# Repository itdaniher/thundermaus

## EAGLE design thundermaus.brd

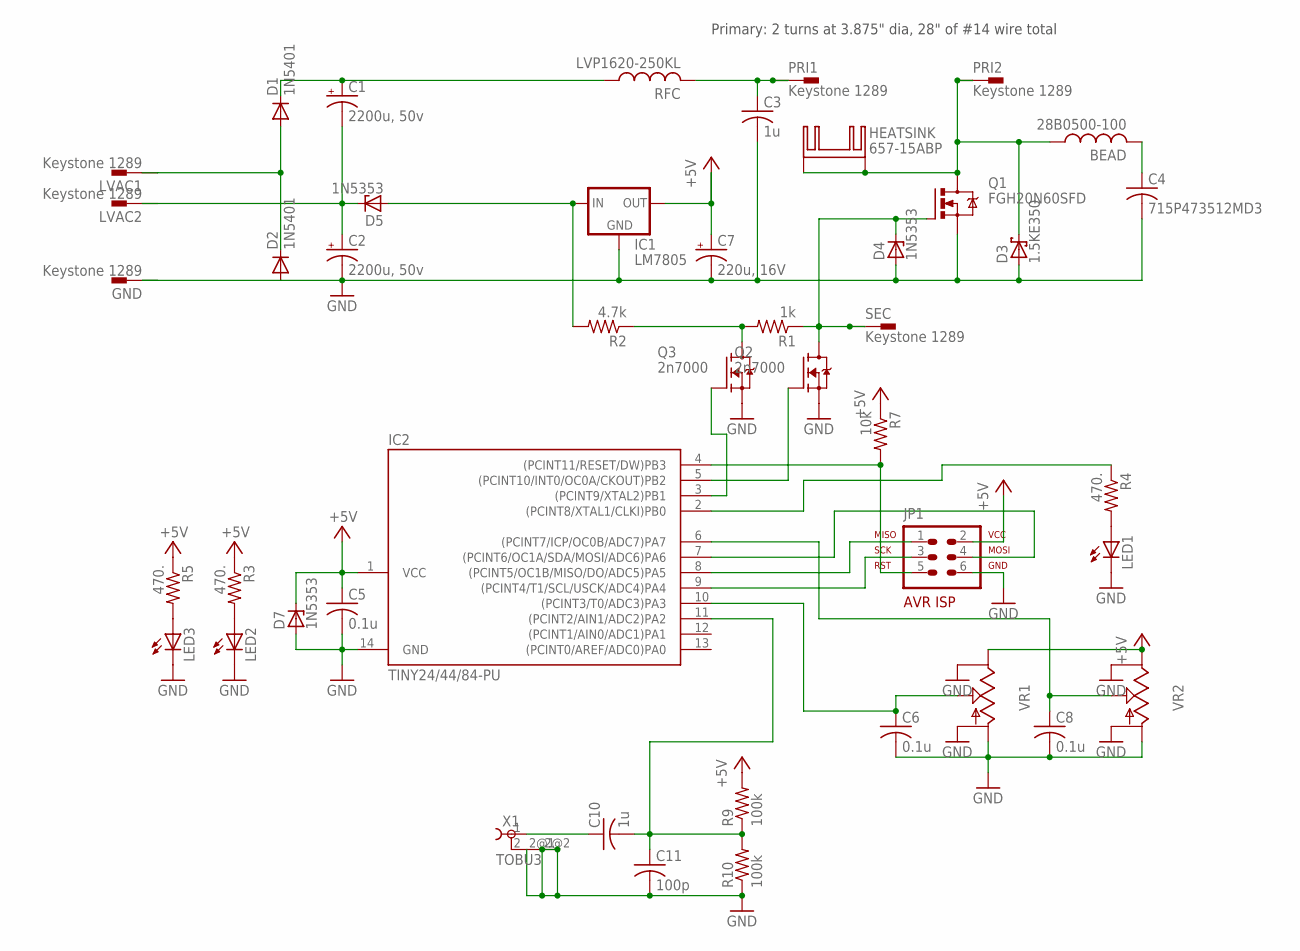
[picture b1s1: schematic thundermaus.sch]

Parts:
BEAD: 28B0500-100; 0207/10
C1, C2: 2200u, 50v; E7,5-16
C3: 1u; C225-062X268
C4: 715P473512MD3; C325-182X374
C5, C6, C8: 0.1u; C025-025X050
C7: 220u, 16V; E2,5-7
C10: 1u; C025-025X050
C11: 100p; C025-025X050
D1, D2: 1N5401; DO201-15
D3: 1.5KE350; DO201T15
D4, D5, D7: 1N5353; C1702-15
GND: Keystone 1289; F061.060
HEATSINK: 657-15ABP; SK129
IC1: LM7805; 78XXS
IC2: TINY24/44/84-PU; DIL14
JP1: AVR-ISP-6VERT; AVR-ISP-6
LED1, LED2, LED3: LED5MM
LVAC1, LVAC2: Keystone 1289; F061.060
PRI1, PRI2: Keystone 1289; F061.060
Q1: FGH20N60SFD; TO247BV
Q2, Q3: 2n7000; TO237-SW
R1: 1k; 0207/10
R2: 4.7k; 0207/10
R3, R4, R5: 470.; 0207/10
R7: 10k; 0207/10
R9, R10: 100k; 0207/10
RFC: LVP1620-250KL; TJ4-U1
SEC: Keystone 1289; F061.060
VR1, VR2: PTV09
X1: TOBU3

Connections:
+5V: C5.1, C7.+, D7.C, IC1.OUT, IC2.1 (VCC), JP1.2, R3.1, R5.1, R7.1, R9.2, VR1.P1 (E), VR2.P1 (E)
GND: C2.-, C3.2, C4.2, C5.2, C6.2, C7.-, C8.2, C11.2, D2.A, D3.A, D4.A, D7.A, GND.A1 (1), GND.A2 (1.1), IC1.GND, IC2.14 (GND), JP1.6, LED1.K (C), LED2.K (C), LED3.K (C), Q1.S, Q2.3 (S), Q3.3 (S), R10.1, VR1.P3 (A), VR1.P$4, VR1.P$5, VR2.P3 (A), VR2.P$4, VR2.P$5, X1.2, X1.2@1 (3), X1.2@2 (4)
unnamed: LED2.A, R3.2
unnamed: D5.A, IC1.IN, R2.2
unnamed: IC2.5 ((PCINT10/INT0/OC0A/CKOUT)PB2), Q2.2 (G)
unnamed: C1.+, D1.C, RFC.1
unnamed: C3.1, PRI1.A1 (1), PRI1.A2 (1.1), RFC.2
unnamed: Q3.1 (D), R1.2, R2.1
unnamed: BEAD.2, C4.1
unnamed: IC2.3 ((PCINT9/XTAL2)PB1), Q3.2 (G)
unnamed: IC2.7 ((PCINT6/OC1A/SDA/MOSI/ADC6)PA6), JP1.4
unnamed: LED3.A, R5.2
unnamed: D4.C, Q1.G, Q2.1 (D), R1.1, SEC.A1 (1), SEC.A2 (1.1)
unnamed: LED1.A, R4.2
unnamed: IC2.8 ((PCINT5/OC1B/MISO/DO/ADC5)PA5), JP1.1
unnamed: IC2.9 ((PCINT4/T1/SCL/USCK/ADC4)PA4), JP1.3
unnamed: IC2.4 ((PCINT11/RESET/DW)PB3), JP1.5, R7.2
unnamed: C6.1, IC2.10 ((PCINT3/T0/ADC3)PA3), VR1.P2 (S)
unnamed: IC2.2 ((PCINT8/XTAL1/CLKI)PB0), R4.1
unnamed: BEAD.1, D3.C, HEATSINK.A2,5, HEATSINK.B2,5, PRI2.A1 (1), PRI2.A2 (1.1), Q1.D
unnamed: C1.-, C2.+, D5.C, LVAC2.A1 (1), LVAC2.A2 (1.1)
unnamed: C10.1, X1.1
unnamed: C10.2, C11.1, IC2.11 ((PCINT2/AIN1/ADC2)PA2), R9.1, R10.2
unnamed: D1.A, D2.C, LVAC1.A1 (1), LVAC1.A2 (1.1)
unnamed: C8.1, IC2.6 ((PCINT7/ICP/OC0B/ADC7)PA7), VR2.P2 (S)

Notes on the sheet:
Primary: 2 turns at 3.875" dia, 28" of #14 wire total

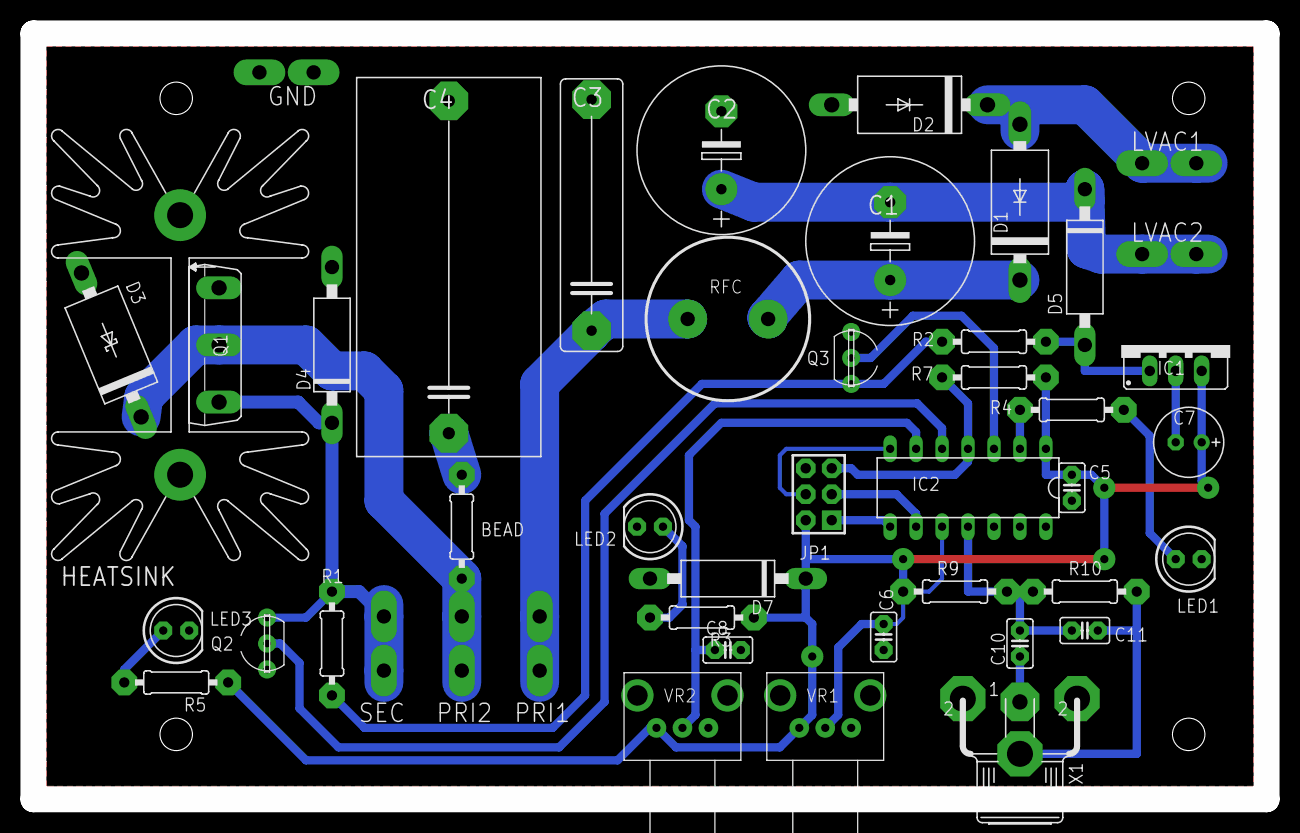
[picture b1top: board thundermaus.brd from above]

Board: 2 copper layers, 120.6 x 74.9 mm, 45 parts (0 on the bottom side), 25 nets.

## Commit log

2012-11-29 initial commit of thundermouse firmware and hardware
2012-11-29 s/rev1/rev2/ - thundermouse with modifications
2012-11-29 added readme w/ todo list for v3
2012-11-29 added makefile, fixed thundermaus.c usage of _delay_us() macro such that it compiles
2012-12-01 rename to sanify
2012-12-12 test firmware for tuning
2012-12-12 start at documentation
2012-12-12 slight modifications to thundermaus code
2012-12-12 update fuse bits to have BOD at right voltage
2012-12-12 update TODO
2012-12-12 drop old .hex
2012-12-12 name all the things
2012-12-13 fix readme formatting
2012-12-13 add assembly documentation
2012-12-13 added DXF of final case design
2012-12-15 added schematic
2013-03-11 rename files
